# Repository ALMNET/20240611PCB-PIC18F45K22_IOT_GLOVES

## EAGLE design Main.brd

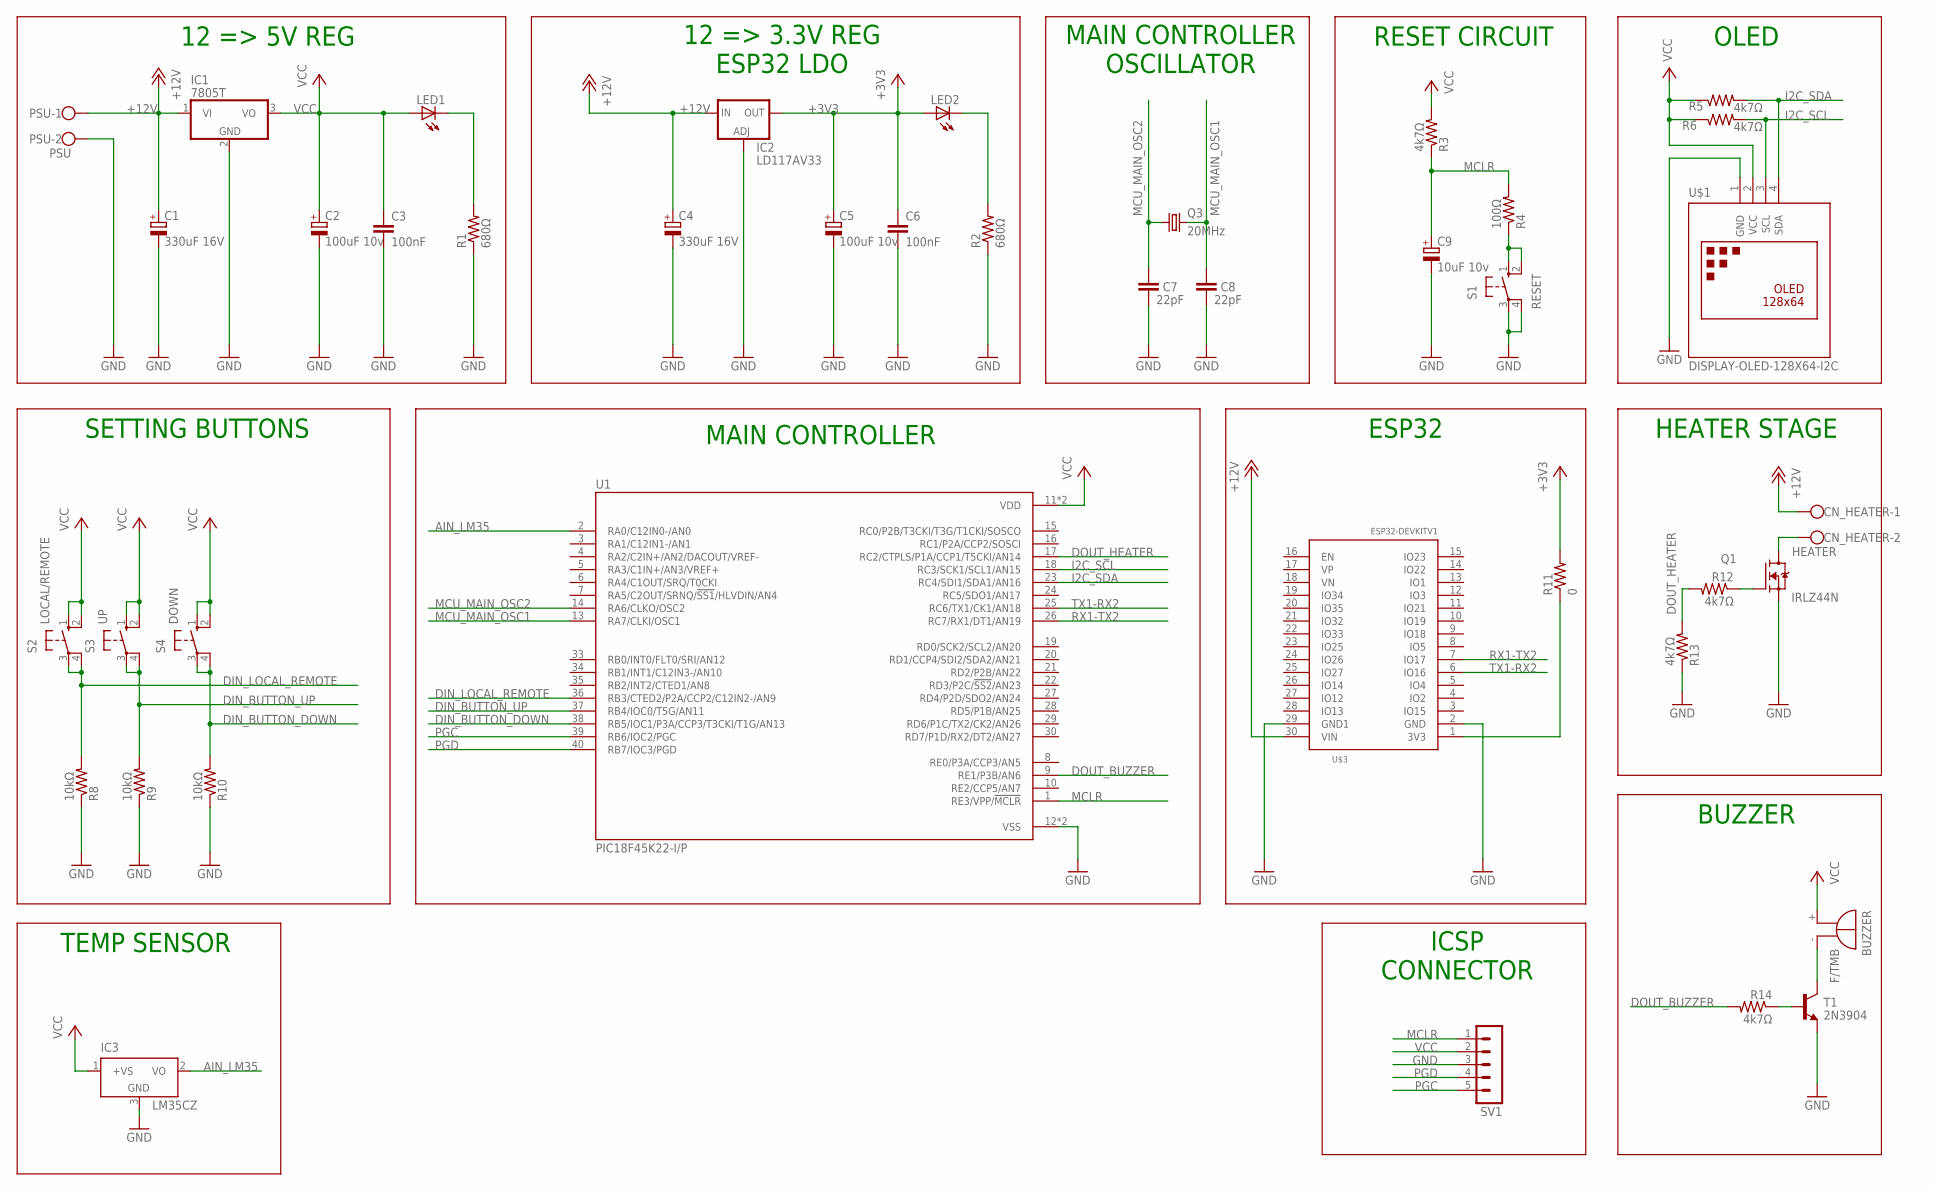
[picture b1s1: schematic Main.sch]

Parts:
BUZZER: F/TMB
C1, C4: 330uF 16V; E2-5
C2, C5: 100uF 10v; E2-5
C3, C6: 100nF; C025-060X050
C7, C8: 22pF; C025-024X044
C9: 10uF 10v; E2-5
CN_HEATER: HEATER; W237-102
IC1: 7805T; TO220H
IC2: LD117AV33; TO220L1
IC3: LM35CZ; TO92
LED1, LED2: LED5MM
PSU: PSU; W237-102
Q1: IRLZ44N; TO254P1054X469X1930-3
Q3: 20MHz; HC49/S
R1, R2: 680Ω; 0204/7
R3, R5, R6, R12, R13, R14: 4k7Ω; 0204/7
R4: 100Ω; 0204/7
R8, R9, R10: 10kΩ; 0204/7
R11: 0; 0204/7
S1: RESET; B3F-10XX
S2: LOCAL/REMOTE; B3F-10XX
S3: UP; B3F-10XX
S4: DOWN; B3F-10XX
SV1: MA05-1
T1: 2N3904; TO92
U1: PIC18F45K22-I/P; DIP1543W47P254L5321H635Q40
U$1: DISPLAY-OLED-128X64-I2C
U$3: ESP32DEVKITV1; ESP32-DEVKITV1

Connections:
+3V3: C5.+, C6.1, IC2.2 (OUT), LED2.A, R11.2
+12V: C1.+, C4.+, CN_HEATER.1, IC1.1 (VI), IC2.3 (IN), PSU.1, U$3.30 (VIN)
AIN_LM35: IC3.2 (VO), U1.2 (RA0/C12IN0-/AN0)
DIN_BUTTON_DOWN: R10.2, S4.3, S4.4 (P1), U1.38 (RB5/IOC1/P3A/CCP3/T3CKI/T1G/AN13)
DIN_BUTTON_UP: R9.2, S3.3, S3.4 (P1), U1.37 (RB4/IOC0/T5G/AN11)
DIN_LOCAL_REMOTE: R8.2, S2.3, S2.4 (P1), U1.36 (RB3/CTED2/P2A/CCP2/C12IN2-/AN9)
DOUT_BUZZER: R14.2, U1.9 (RE1/P3B/AN6)
DOUT_HEATER: R12.2, R13.2, U1.17 (RC2/CTPLS/P1A/CCP1/T5CKI/AN14)
GND: C1.-, C2.-, C3.2, C4.-, C5.-, C6.2, C7.2, C8.2, C9.-, IC1.2 (GND), IC2.1 (ADJ), IC3.3 (GND), PSU.2, Q1.3 (S), R1.1, R2.1, R8.1, R9.1, R10.1, R13.1, S1.3, S1.4 (P1), SV1.3, T1.3 (E), U1.12 (VSS), U1.31 (VSS), U$1.1 (GND), U$3.2 (GND), U$3.29 (GND1)
I2C_SCL: R6.2, U1.18 (RC3/SCK1/SCL1/AN15), U$1.3 (SCL)
I2C_SDA: R5.2, U1.23 (RC4/SDI1/SDA1/AN16), U$1.4 (SDA)
MCLR: C9.+, R3.1, R4.2, SV1.1, U1.1 (RE3/VPP/!MCLR!)
MCU_MAIN_OSC1: C8.1, Q3.2, U1.13 (RA7/CLKI/OSC1)
MCU_MAIN_OSC2: C7.1, Q3.1, U1.14 (RA6/CLKO/OSC2)
unnamed: LED2.K (C), R2.2
unnamed: R11.1, U$3.1 (3V3)
unnamed: LED1.K (C), R1.2
unnamed: R4.1, S1.1 (S), S1.2 (S1)
unnamed: R14.1, T1.2 (B)
unnamed: BUZZER.-, T1.1 (C)
unnamed: Q1.1 (G), R12.1
unnamed: CN_HEATER.2, Q1.2 (D)
PGC: SV1.5, U1.39 (RB6/IOC2/PGC)
PGD: SV1.4, U1.40 (RB7/IOC3/PGD)
RX1-TX2: U1.26 (RC7/RX1/DT1/AN19), U$3.7 (IO17)
TX1-RX2: U1.25 (RC6/TX1/CK1/AN18), U$3.6 (IO16)
VCC: BUZZER.+, C2.+, C3.1, IC1.3 (VO), IC3.1 (+VS), LED1.A, R3.2, R5.1, R6.1, S2.1 (S), S2.2 (S1), S3.1 (S), S3.2 (S1), S4.1 (S), S4.2 (S1), SV1.2, U1.11 (VDD), U1.32 (VDD), U$1.2 (VCC)

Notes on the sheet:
12 => 5V REG
12 => 3.3V REG ESP32 LDO
ESP32
OLED
HEATER STAGE
SETTING BUTTONS
BUZZER
MAIN CONTROLLER OSCILLATOR
ICSP CONNECTOR
RESET CIRCUIT
TEMP SENSOR
MAIN CONTROLLER

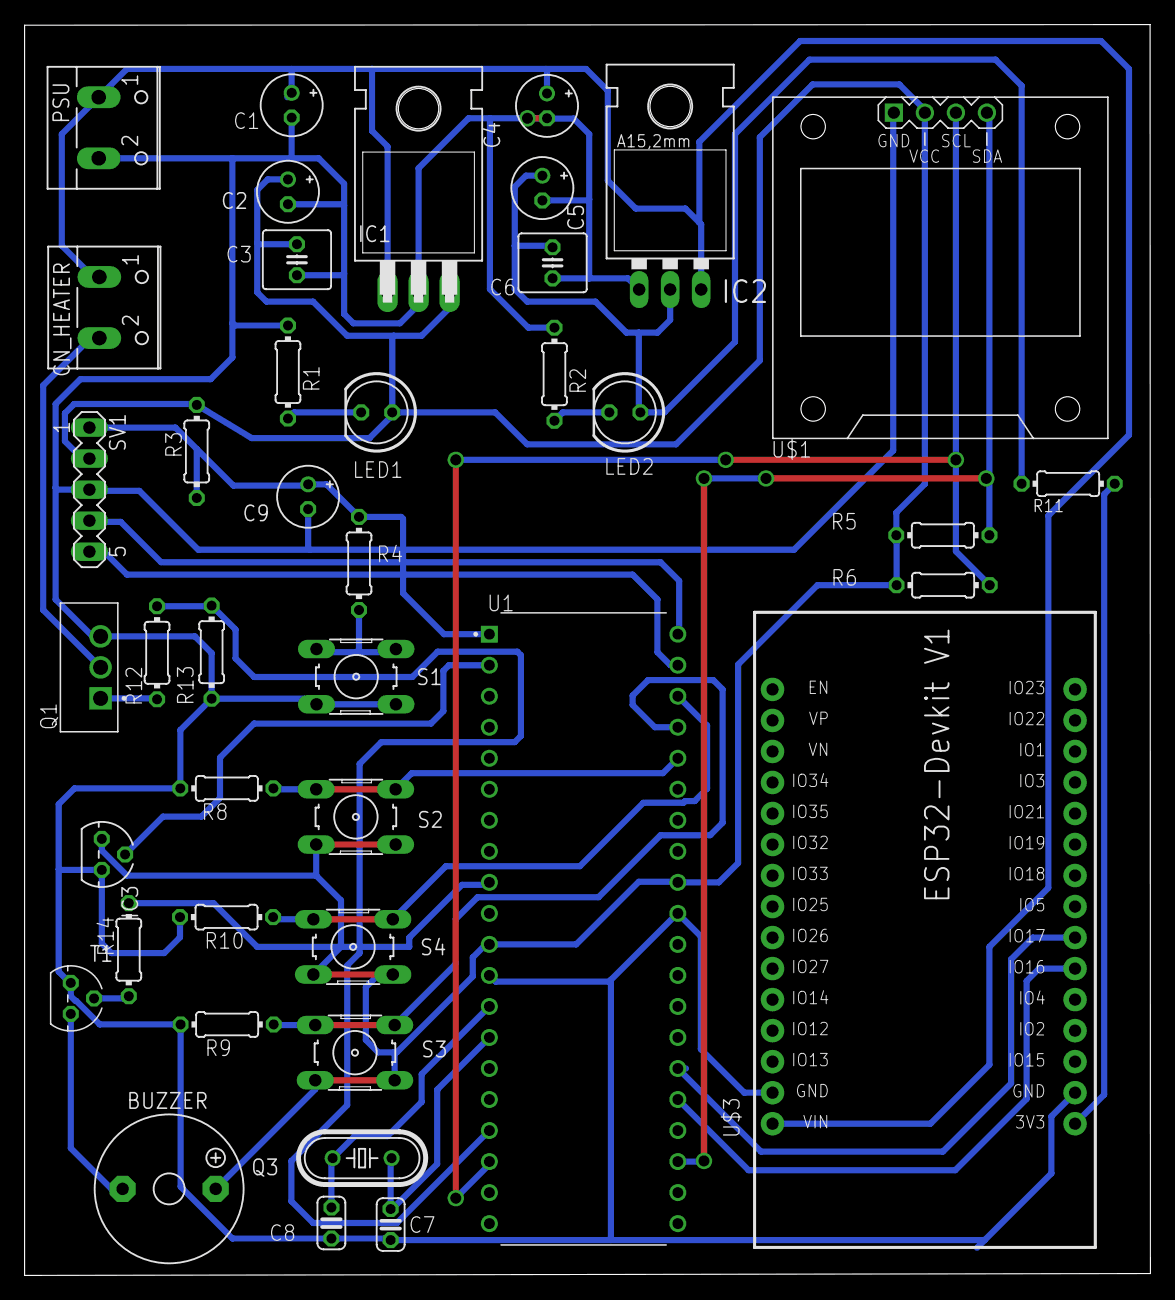
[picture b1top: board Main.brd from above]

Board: 2 copper layers, 92.2 x 102.4 mm, 41 parts (0 on the bottom side), 27 nets.

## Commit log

2024-06-30 Schematic Rearranged
2024-06-30 Renamed Resistors and capacitors
2024-06-30 Components placed, Previous to start routing
2024-06-30 Routing. I2C lines Pending
2024-06-30 Routing complete, Pending swap routes from top to botton
2024-06-30 Routing complete, Checking routes and design
2024-06-30 Ready to deliver

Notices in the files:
parts and their libraries:
diy-modules: Released under the Creative Commons Attribution 4.0 International License: http://creativecommons.org/licenses/by/4.0
